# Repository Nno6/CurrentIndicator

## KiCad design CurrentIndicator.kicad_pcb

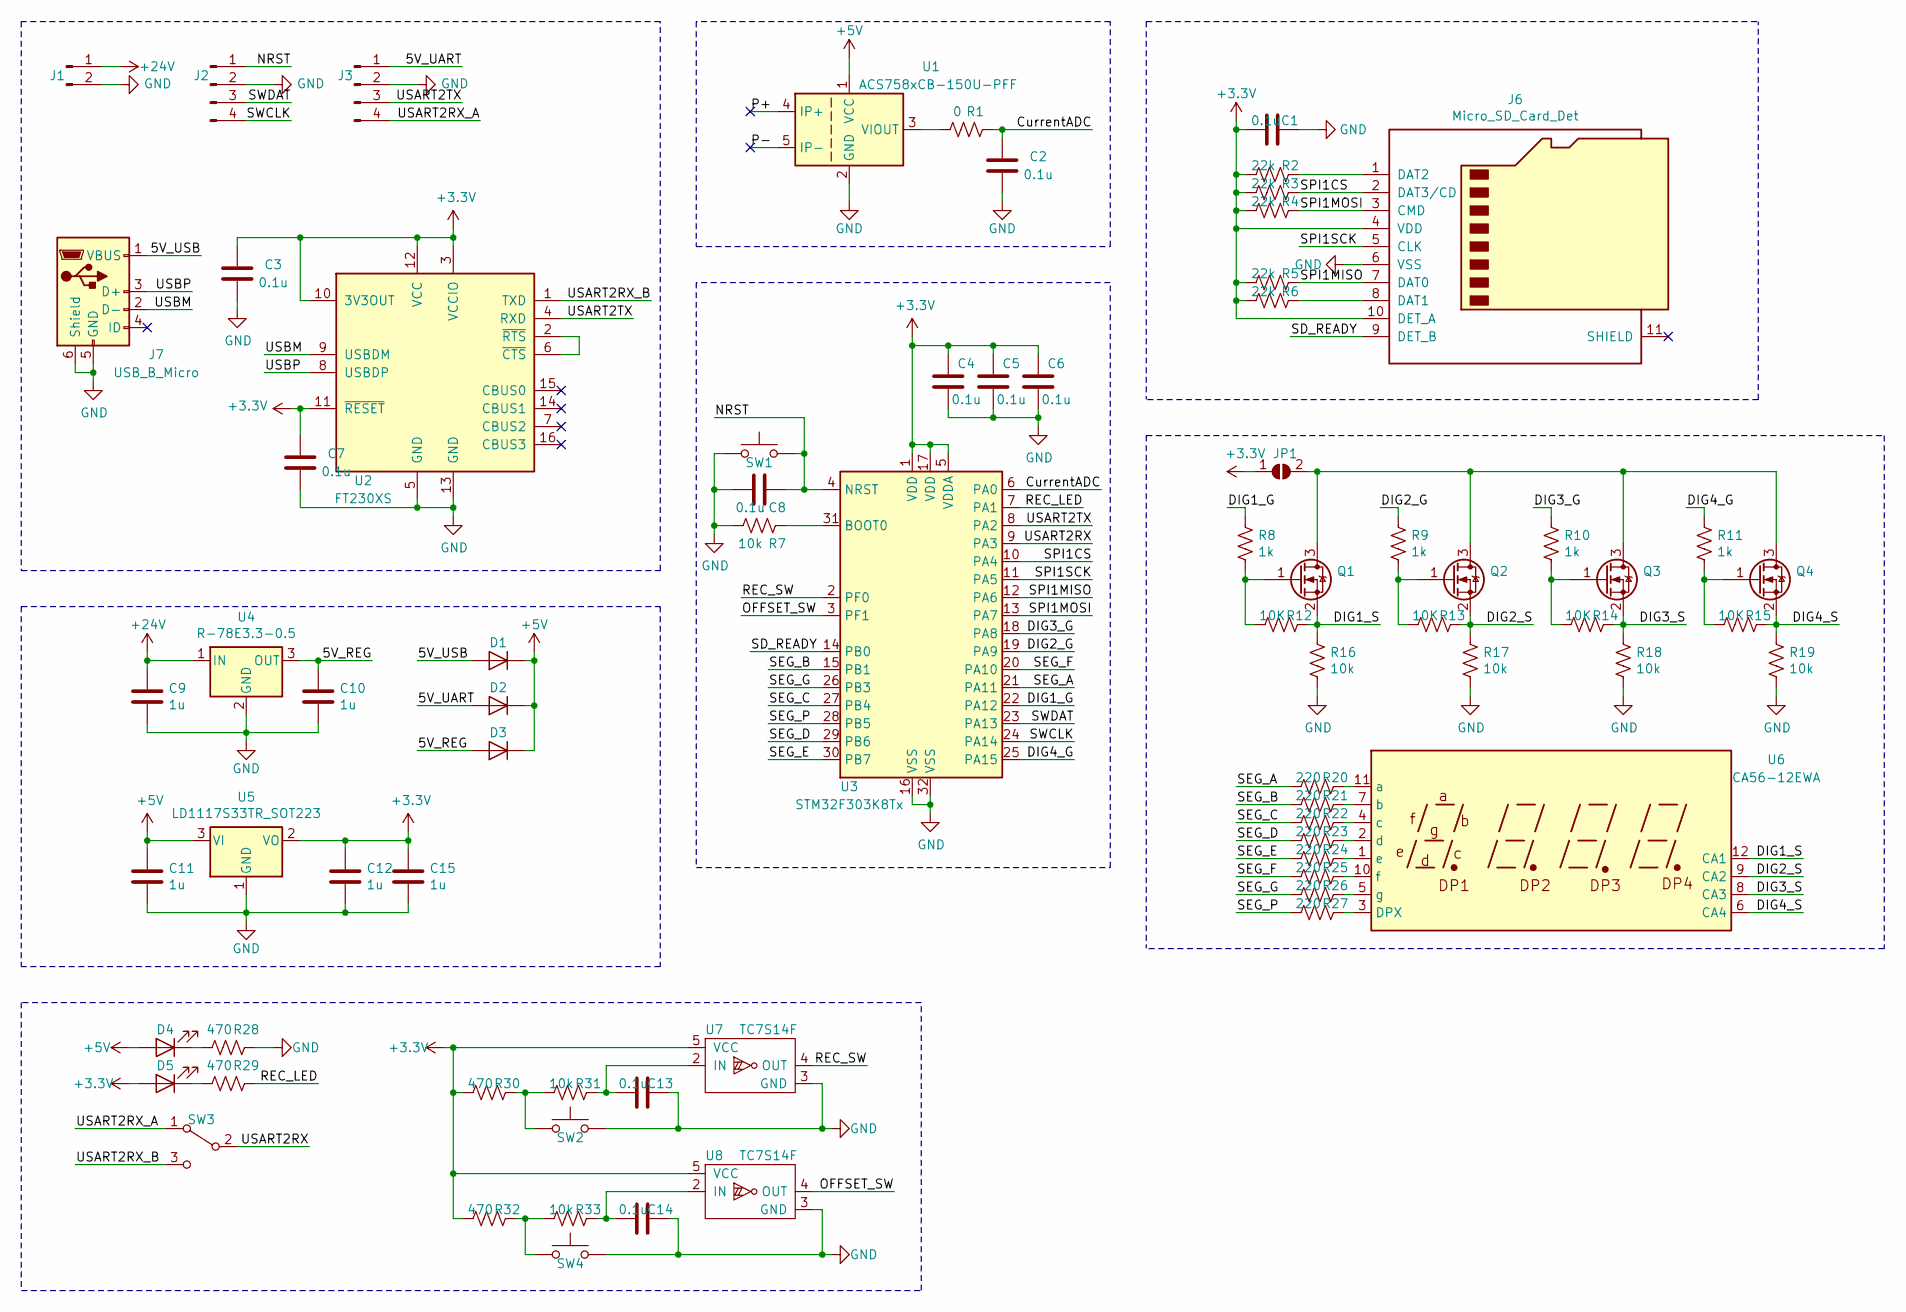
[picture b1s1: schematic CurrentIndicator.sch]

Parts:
C1, C2, C3, C4, C5, C6, C7, C8, C13, C14: 0.1u; C_0603_1608Metric_Pad1.05x0.95mm_HandSolder
C9, C10, C11, C12, C15: 1u; C_0603_1608Metric_Pad1.05x0.95mm_HandSolder
D1, D2, D3: NSR0320MW2T1G; D_SOD-323
D4, D5: LED; LED_0603_1608Metric_Pad1.05x0.95mm_HandSolder
J1: Conn_01x02_Male; XA_2pin_straight
J2, J3: Conn_01x04_Male; PinHeader_1x04_P2.54mm_Vertical
J6: Micro_SD_Card_Det; DM3AT-SF-PEJM5
J7: USB_B_Micro; ZX62R-B-5P
JP1: SolderJumper_2_Open; SolderJumper-2_P1.3mm_Open_TrianglePad1.0x1.5mm
Q1, Q2, Q3, Q4: IRLML6344TRPBFTR; SOT-23
R1: 0; R_0603_1608Metric_Pad1.05x0.95mm_HandSolder
R2, R3, R4, R5, R6: 22k; R_0603_1608Metric_Pad1.05x0.95mm_HandSolder
R7, R16, R17, R18, R19, R31, R33: 10k; R_0603_1608Metric_Pad1.05x0.95mm_HandSolder
R8, R9, R10, R11: 1k; R_0603_1608Metric_Pad1.05x0.95mm_HandSolder
R12, R13, R14, R15: 10K; R_0603_1608Metric_Pad1.05x0.95mm_HandSolder
R20, R21, R22, R23, R24, R25, R26, R27: 220; R_0603_1608Metric_Pad1.05x0.95mm_HandSolder
R28, R29, R30, R32: 470; R_0603_1608Metric_Pad1.05x0.95mm_HandSolder
SW1: TVAF06-A020B-R
SW2, SW4: TS-0606-F-N; TS-0606
SW3: IS-1235-G
U1: ACS758xCB-150U-PFF; Allegro_CB_PFF
U2: FT230XS; SSOP-16_3.9x4.9mm_P0.635mm
U3: STM32F303K8Tx; LQFP-32_7x7mm_P0.8mm
U4: R-78E3.3-0.5; Converter_DCDC_RECOM_R-78E-0.5_THT
U5: LD1117S33TR_SOT223; SOT-223-3_TabPin2
U6: CA56-12EWA
U7, U8: TC7S14F; SOT-23-5_HandSoldering

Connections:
+3V3: C1.1, C3.1, C4.1, C5.1, C6.1, C7.1, C12.1, C15.1, D5.2 (A), J6.4 (VDD), J6.10 (DET_A), JP1.1 (A), R2.1, R3.1, R4.1, R5.1, R6.1, R30.1, R32.1, U2.3 (VCCIO), U2.10 (3V3OUT), U2.11 (~RESET), U2.12 (VCC), U3.1 (VDD), U3.5 (VDDA), U3.17 (VDD), U5.2 (VO), U7.5 (VCC), U8.5 (VCC)
+5V: C11.1, D1.1 (K), D2.1 (K), D3.1 (K), D4.2 (A), U1.1 (VCC), U5.3 (VI)
+24V: C9.1, J1.1, U4.1 (IN)
/5V_REG: C10.1, D3.2 (A), U4.3 (OUT)
/5V_UART: D2.2 (A), J3.1
/5V_USB: D1.2 (A), J7.1 (VBUS)
/CurrentADC: C2.1, R1.2, U3.6 (PA0)
/DIG1_G: R8.1, U3.22 (PA12)
/DIG1_S: Q1.2 (S), R12.2, R16.1, U6.12 (CA1)
/DIG2_G: R9.1, U3.19 (PA9)
/DIG2_S: Q2.2 (S), R13.2, R17.1, U6.9 (CA2)
/DIG3_G: R10.1, U3.18 (PA8)
/DIG3_S: Q3.2 (S), R14.2, R18.1, U6.8 (CA3)
/DIG4_G: R11.1, U3.25 (PA15)
/DIG4_S: Q4.2 (S), R15.2, R19.1, U6.6 (CA4)
/NRST: C8.1, J2.1, SW1.2, U3.4 (NRST)
/OFFSET_SW: U3.3 (PF1), U8.4 (OUT)
/P+: U1.4 (IP+)
/P-: U1.5 (IP-)
/REC_LED: R29.2, U3.7 (PA1)
/REC_SW: U3.2 (PF0), U7.4 (OUT)
/SD_READY: J6.9 (DET_B), U3.14 (PB0)
/SEG_A: R20.1, U3.21 (PA11)
/SEG_B: R21.1, U3.15 (PB1)
/SEG_C: R22.1, U3.27 (PB4)
/SEG_D: R23.1, U3.29 (PB6)
/SEG_E: R24.1, U3.30 (PB7)
/SEG_F: R25.1, U3.20 (PA10)
/SEG_G: R26.1, U3.26 (PB3)
/SEG_P: R27.1, U3.28 (PB5)
/SPI1CS: J6.2 (DAT3/CD), R3.2, U3.10 (PA4)
/SPI1MISO: J6.7 (DAT0), R5.2, U3.12 (PA6)
/SPI1MOSI: J6.3 (CMD), R4.2, U3.13 (PA7)
/SPI1SCK: J6.5 (CLK), U3.11 (PA5)
/SWCLK: J2.4, U3.24 (PA14)
/SWDAT: J2.3, U3.23 (PA13)
/USART2RX: SW3.2 (B), U3.9 (PA3)
/USART2RX_A: J3.4, SW3.1 (A)
/USART2RX_B: SW3.3 (C), U2.1 (TXD)
/USART2TX: J3.3, U2.4 (RXD), U3.8 (PA2)
/USBM: J7.2 (D-), U2.9 (USBDM)
/USBP: J7.3 (D+), U2.8 (USBDP)
GND: C1.2, C2.2, C3.2, C4.2, C5.2, C6.2, C7.2, C8.2, C9.2, C10.2, C11.2, C12.2, C13.2, C14.2, C15.2, J1.2, J2.2, J3.2, J6.6 (VSS), J7.5 (GND), J7.6 (Shield), R7.2, R16.2, R17.2, R18.2, R19.2, R28.2, SW1.1, SW2.2, SW4.2, U1.2 (GND), U2.5 (GND), U2.13 (GND), U3.16 (VSS), U3.32 (VSS), U4.2 (GND), U5.1 (GND), U7.3 (GND), U8.3 (GND)
unnamed: C13.1, R31.2, U7.2 (IN)
unnamed: C14.1, R33.2, U8.2 (IN)
unnamed: D4.1 (K), R28.1
unnamed: D5.1 (K), R29.1
unnamed: J6.1 (DAT2), R2.2
unnamed: J6.8 (DAT1), R6.2
unnamed: JP1.2 (B), Q1.3 (D), Q2.3 (D), Q3.3 (D), Q4.3 (D)
unnamed: Q1.1 (G), R8.2, R12.1
unnamed: Q2.1 (G), R9.2, R13.1
unnamed: Q3.1 (G), R10.2, R14.1
unnamed: Q4.1 (G), R11.2, R15.1
unnamed: R1.1, U1.3 (VIOUT)
unnamed: R7.1, U3.31 (BOOT0)
unnamed: R20.2, U6.11 (a)
unnamed: R21.2, U6.7 (b)
unnamed: R22.2, U6.4 (c)
unnamed: R23.2, U6.2 (d)
unnamed: R24.2, U6.1 (e)
unnamed: R25.2, U6.10 (f)
unnamed: R26.2, U6.5 (g)
unnamed: R27.2, U6.3 (DPX)
unnamed: R30.2, R31.1, SW2.1
unnamed: R32.2, R33.1, SW4.1
unnamed: U2.2 (~RTS), U2.6 (~CTS)

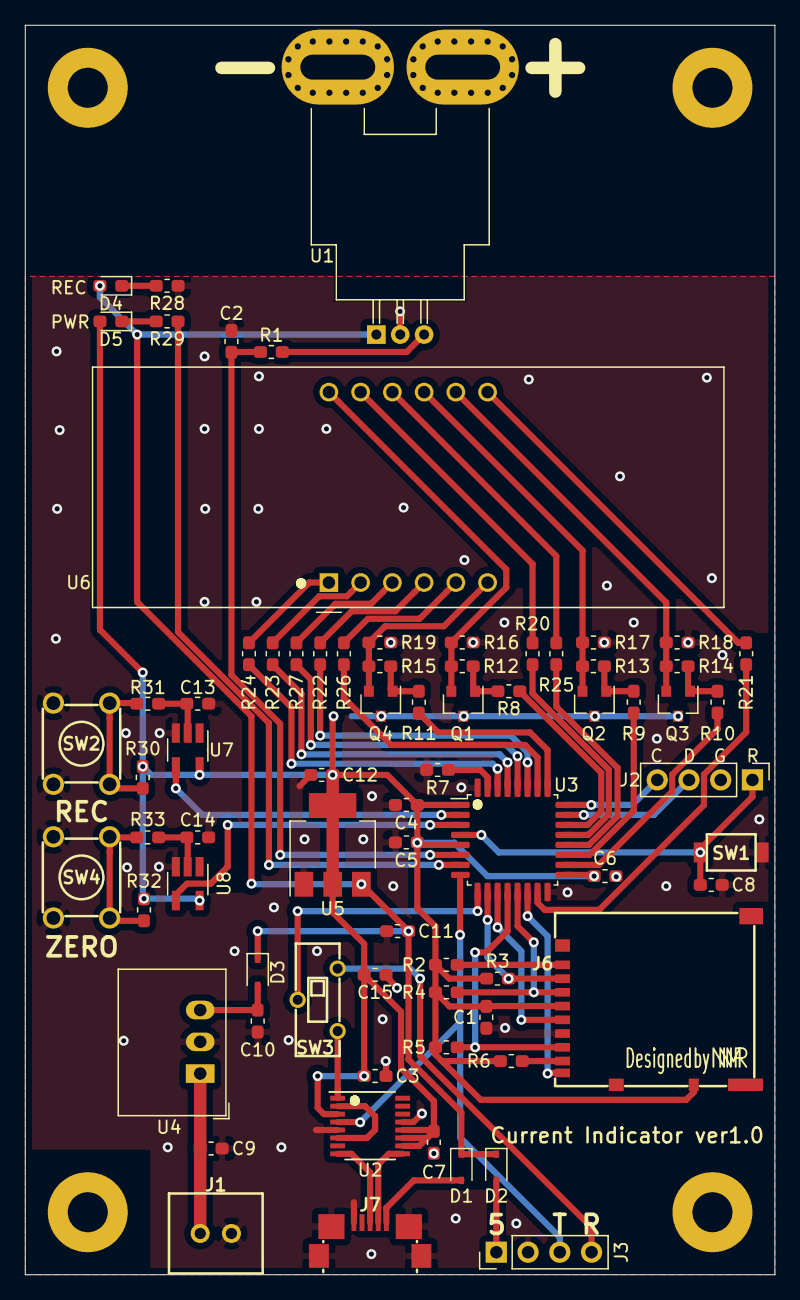
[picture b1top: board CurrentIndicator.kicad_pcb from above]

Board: 2 copper layers, 60.0 x 100.0 mm, 75 parts (1 on the bottom side), 65 nets.

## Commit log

2020-11-18 いにちあｌ こっみｔ 第一発注
2020-12-18 シュミットトリガのピン配置修正
